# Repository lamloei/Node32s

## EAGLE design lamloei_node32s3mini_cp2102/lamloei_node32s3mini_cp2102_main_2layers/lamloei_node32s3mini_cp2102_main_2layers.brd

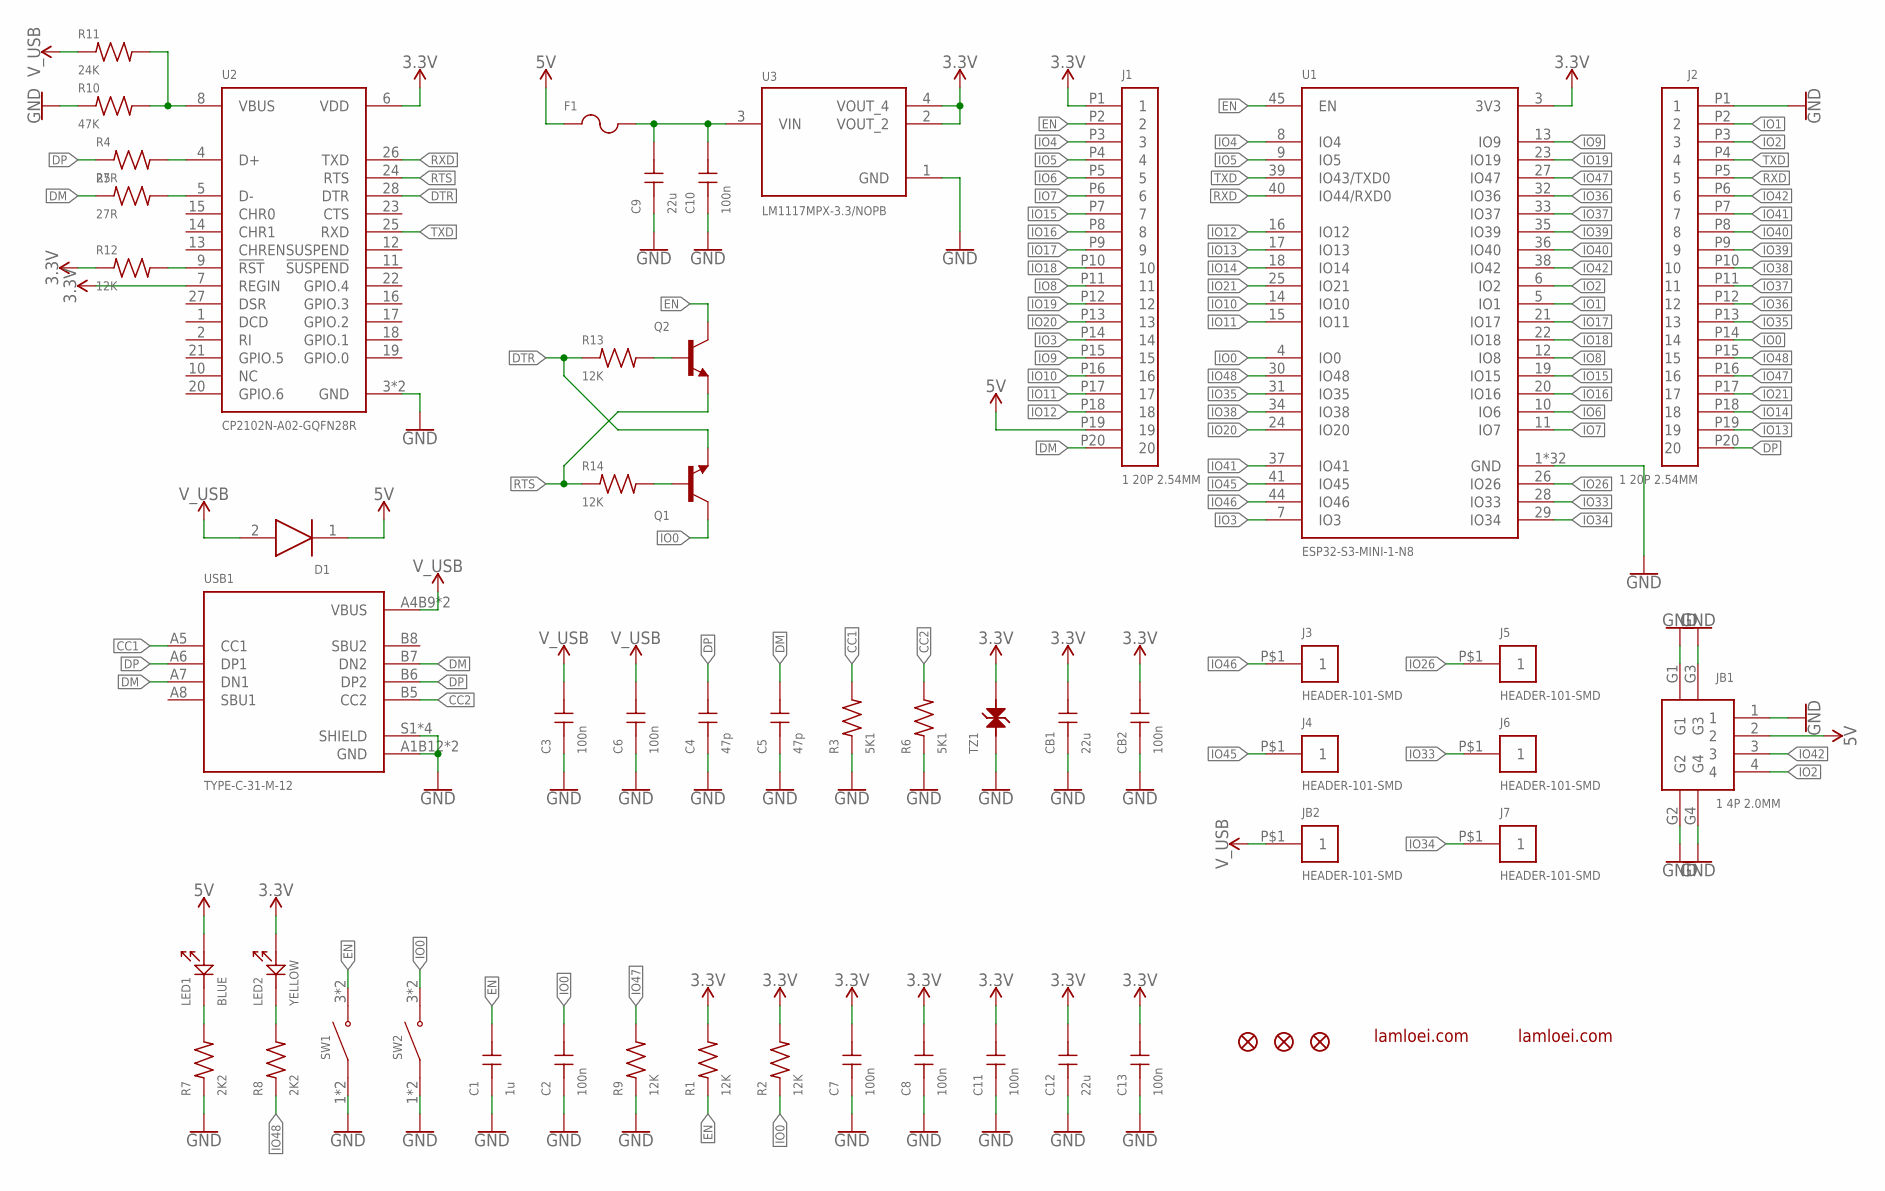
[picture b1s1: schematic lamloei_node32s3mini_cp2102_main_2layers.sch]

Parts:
C1: 1u; GRM155R70J105KA12D
C2, C3, C6, C7, C8, C10, C11, C13: 100n; GCM155R71H104KE02D
C4, C5: 47p; GCM1555C1H470JA16D
C9, C12: 22u; GCM21BR71H105KA03L
CB1: 22u; GCM21BR71H105KA03L
CB2: 100n; GCM155R71H104KE02D
D1: PMEG4050EP,115
F1: MF-NSMF050-2
J1, J2: 1 20P 2.54MM; HEADER-120
J3, J4, J5, J6, J7: HEADER-101-SMD
JB1: 1 4P 2.0MM; A2012WR-S-4P
JB2: HEADER-101-SMD
LED1: BLUE; 19-217BHC-ZL1M2RY3T
LED2: YELLOW; 19-213/Y2C-CQ2R2L/3T(CY)
Q1, Q2: BC847B,215
R1, R2, R9, R12, R13, R14: 12K; R0402
R3, R6: 5K1; R0402
R4, R5: 27R; R0402
R7, R8: 2K2; R0402
R10: 47K; R0402
R11: 24K; R0402
SW1, SW2: K2-1808SN-A4SW-01
TZ1: LXES15AAA1-153
U1: ESP32-S3-MINI-1-N8
U2: CP2102N-A02-GQFN28R
U3: LM1117MPX-3.3/NOPB
USB1: TYPE-C-31-M-12
ZFD1, ZFD2, ZFD3: FIDUCIAL1X2; FIDUCIAL-1X2
ZL1, ZL2: LAMLEOI_LOGO_3

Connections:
3.3V: C7.2, C8.2, C11.2, C12.2, C13.2, CB1.2, CB2.2, J1.P1 (1), LED2.2, R1.2, R2.2, R12.1, TZ1.2, U1.3 (3V3), U2.6 (VDD), U2.7 (REGIN), U3.2 (VOUT_2), U3.4 (VOUT_4)
5V: D1.1 (K), F1.1, J1.P19 (19), JB1.2, LED1.2
CC1: R3.2, USB1.A5 (CC1)
CC2: R6.2, USB1.B5 (CC2)
DM: C5.2, J1.P20 (20), R5.1, USB1.A7 (DN1), USB1.B7 (DN2)
DP: C4.2, J2.P20 (20), R4.1, USB1.A6 (DP1), USB1.B6 (DP2)
DTR: Q1.E, R13.1, U2.28 (DTR)
EN: C1.2, J1.P2 (2), Q2.C, R1.1, SW1.3 (NO), SW1.4 (NO), U1.45 (EN)
GND: C1.1, C2.1, C3.1, C4.1, C5.1, C6.1, C7.1, C8.1, C9.1, C10.1, C11.1, C12.1, C13.1, CB1.1, CB2.1, J2.P1 (1), JB1.1, JB1.G1, JB1.G2, JB1.G3, JB1.G4, R3.1, R6.1, R7.1, R9.1, R10.1, SW1.1 (COM), SW1.2 (COM), SW2.1 (COM), SW2.2 (COM), TZ1.1, U1.1 (GND), U1.2 (GND), U1.42 (GND), U1.43 (GND), U1.46 (GND), U1.47 (GND), U1.48 (GND), U1.49 (GND), U1.50 (GND), U1.51 (GND), U1.52 (GND), U1.53 (GND), U1.54 (GND), U1.55 (GND), U1.56 (GND), U1.57 (GND), U1.58 (GND), U1.59 (GND), U1.60 (GND), U1.61 (GND), U1.61_1 (GND), U1.61_2 (GND), U1.61_3 (GND), U1.61_4 (GND), U1.61_5 (GND), U1.61_6 (GND), U1.61_7 (GND), U1.61_8 (GND), U1.62 (GND), U1.63 (GND), U1.64 (GND), U1.65 (GND), U2.3 (GND), U2.29 (GND), U3.1 (GND), USB1.A1B12 (GND), USB1.B1A12 (GND), USB1.S1 (SHIELD), USB1.S2 (SHIELD), USB1.S3 (SHIELD), USB1.S4 (SHIELD)
GPIO.5: U2.21 (GPIO.5)
IO0: C2.2, J2.P14 (14), Q1.C, R2.1, SW2.3 (NO), SW2.4 (NO), U1.4 (IO0)
IO1: J2.P2 (2), U1.5 (IO1)
IO2: J2.P3 (3), JB1.4, U1.6 (IO2)
IO3: J1.P14 (14), U1.7 (IO3)
IO4: J1.P3 (3), U1.8 (IO4)
IO5: J1.P4 (4), U1.9 (IO5)
IO6: J1.P5 (5), U1.10 (IO6)
IO7: J1.P6 (6), U1.11 (IO7)
IO8: J1.P11 (11), U1.12 (IO8)
IO9: J1.P15 (15), U1.13 (IO9)
IO10: J1.P16 (16), U1.14 (IO10)
IO11: J1.P17 (17), U1.15 (IO11)
IO12: J1.P18 (18), U1.16 (IO12)
IO13: J2.P19 (19), U1.17 (IO13)
IO14: J2.P18 (18), U1.18 (IO14)
IO15: J1.P7 (7), U1.19 (IO15)
IO16: J1.P8 (8), U1.20 (IO16)
IO17: J1.P9 (9), U1.21 (IO17)
IO18: J1.P10 (10), U1.22 (IO18)
IO19: J1.P12 (12), U1.23 (IO19)
IO20: J1.P13 (13), U1.24 (IO20)
IO21: J2.P17 (17), U1.25 (IO21)
IO26: J5.P$1, U1.26 (IO26)
IO33: J6.P$1, U1.28 (IO33)
IO34: J7.P$1, U1.29 (IO34)
IO35: J2.P13 (13), U1.31 (IO35)
IO36: J2.P12 (12), U1.32 (IO36)
IO37: J2.P11 (11), U1.33 (IO37)
IO38: J2.P10 (10), U1.34 (IO38)
IO39: J2.P9 (9), U1.35 (IO39)
IO40: J2.P8 (8), U1.36 (IO40)
IO41: J2.P7 (7), U1.37 (IO41)
IO42: J2.P6 (6), JB1.3, U1.38 (IO42)
IO45: J4.P$1, U1.41 (IO45)
IO46: J3.P$1, U1.44 (IO46)
IO47: J2.P16 (16), R9.2, U1.27 (IO47)
IO48: J2.P15 (15), R8.1, U1.30 (IO48)
unnamed: R5.2, U2.5 (D-)
unnamed: R4.2, U2.4 (D+)
unnamed: C9.2, C10.2, F1.2, U3.3 (VIN)
unnamed: LED1.1, R7.2
unnamed: LED2.1, R8.2
unnamed: Q2.B, R13.2
unnamed: Q1.B, R14.2
unnamed: R12.2, U2.9 (!RST)
unnamed: R10.2, R11.2, U2.8 (VBUS)
RTS: Q2.E, R14.1, U2.24 (RTS)
RXD: J2.P5 (5), U1.40 (IO44/RXD0), U2.26 (TXD)
TXD: J2.P4 (4), U1.39 (IO43/TXD0), U2.25 (RXD)
V_USB: C3.2, C6.2, D1.2 (A), JB2.P$1, R11.1, USB1.A4B9 (VBUS), USB1.B4A9 (VBUS)

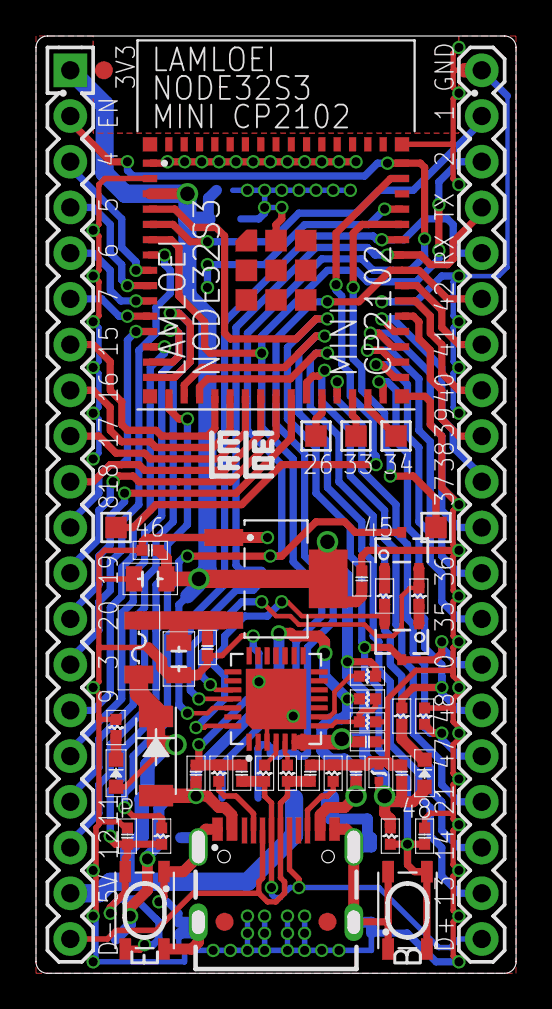
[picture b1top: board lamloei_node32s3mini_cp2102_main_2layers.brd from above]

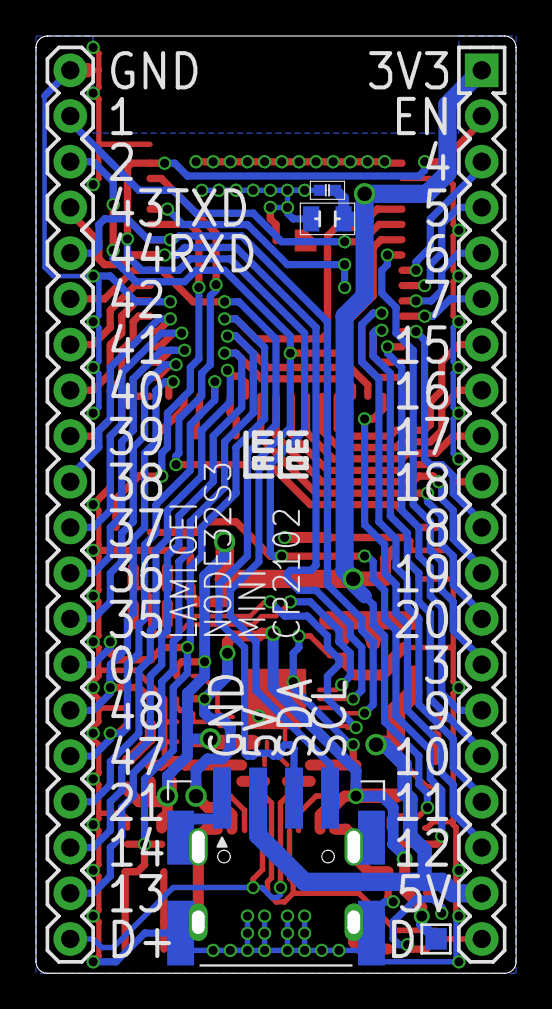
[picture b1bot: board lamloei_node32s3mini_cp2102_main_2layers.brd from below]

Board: 2 copper layers, 26.0 x 51.4 mm, 56 parts (5 on the bottom side), 59 nets.

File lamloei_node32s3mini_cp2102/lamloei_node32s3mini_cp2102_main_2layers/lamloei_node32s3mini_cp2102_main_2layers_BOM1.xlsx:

Comment | Designator | Footprint | LCSC Part #（optional）
Samsung - CL05A105KA5NQNC - 25V 1uF X5R ±10% | C1 | CAP_0402 | C52923
Samsung - CL05B104KO5NNNC - 16V 100nF X7R ±10% | C2, C3, C6, C7, C8, C10, C11, C13 | CAP_0402 | C1525
FH - 0402CG470J500NT - 50V 47pF C0G ±5% | C4, C5 | CAP_0402 | C1567
Samsung - CL21A106KAYNNNE - 25V 10UF X5R ±10% | C9 | CAP_0805 | C15850
Samsung - CL21A476MQYNNNE - 6.3V 47UF X5R ±20% | C12 | CAP_0805 | C16780
Extended - Nexperia - PMEG4020EP,115 - 40V 490mV@2A 2A (SBD) | D1 | SOD-128 | C456125
Extended - BOURNS - MF-NSMF050-2 - 13.2V 1A 1206 PTC | F1 | PTC_1206 | C75464
Everlight Elec - 19-217/BHC-ZL1M2RY/3T - Blue 465~475nm 0603 (LED) | LED1 | LED_0603 | C72041
Everlight Elec - 19-213/Y2C-CQ2R2L/3T(CY) - Yellow 585.5~591.5nm 0603 (LED) | LED2 | LED_0603 | C72038
CJ - S8050 J3Y - Transistors NPN 500mA 25V | Q1, Q2 | SOT-23-3 | C2146
UNI-ROYAL - 0402WGF1202TCE - 12kΩ ±1% 1/16W | R1, R2, R9, R12, R13, R14 | RES_0402 | C25752
UNI-ROYAL - 0402WGF5101TCE - 5.1kΩ ±1% 1/16W | R3, R6 | RES_0402 | C25905
UNI-ROYAL - 0402WGF220JTCE - 22Ω ±1% 1/16W | R4, R5 | RES_0402 | C25092
UNI-ROYAL - 0402WGF2201TCE - 2.2kΩ ±1% 1/16W | R7, R8 | RES_0402 | C25879
UNI-ROYAL - 0402WGF4702TCE - 47kΩ ±1% 1/16W | R10 | RES_0402 | C25792
UNI-ROYAL - 0402WGF2402TCE - 24kΩ ±1% 1/16W | R11 | RES_0402 | C25769
Extended - Korean Hroparts Elec - K2-1808UN-A4SW-04 - SPST 50mA @ 12VDC | SW1 | SMD-4_3.25x2.5x4.2P | C145878
Extended - Korean Hroparts Elec - K2-1808GN-A4SW-04 - SPST 50mA @ 12VDC | SW2 | SMD-4_3.25x2.5x4.2P | C283535
Extended - Murata - LXES15AAA1-153 - Diodes - ESD 0402 | TZ1 | TVS_0402 | C86141
Extended - Espressif - ESP32-S3-MINI-1U-N8 - Module WiFi Modules | U1 | QFN-73_EP_15.4x15.4x0.85P | C2980299
SILICON LABS - CP2102-GMR - Transceiver 1Mbps USB 1/1 | U2 | QFN-28_EP_5.0x5.0x0.5P | C6568
AMS - AMS1117-3.3 - 1A 1.3V@(800mA) Fixed 3.3V~3.3V Positive 1 (LDO) | U3 | SOT-223 | C6186
Extended - Korean Hroparts Elec - TYPE-C-31-M-12 - USB - Type C Female | USB1 | TYPE-C-31_L8.94_W7.3 | C165948

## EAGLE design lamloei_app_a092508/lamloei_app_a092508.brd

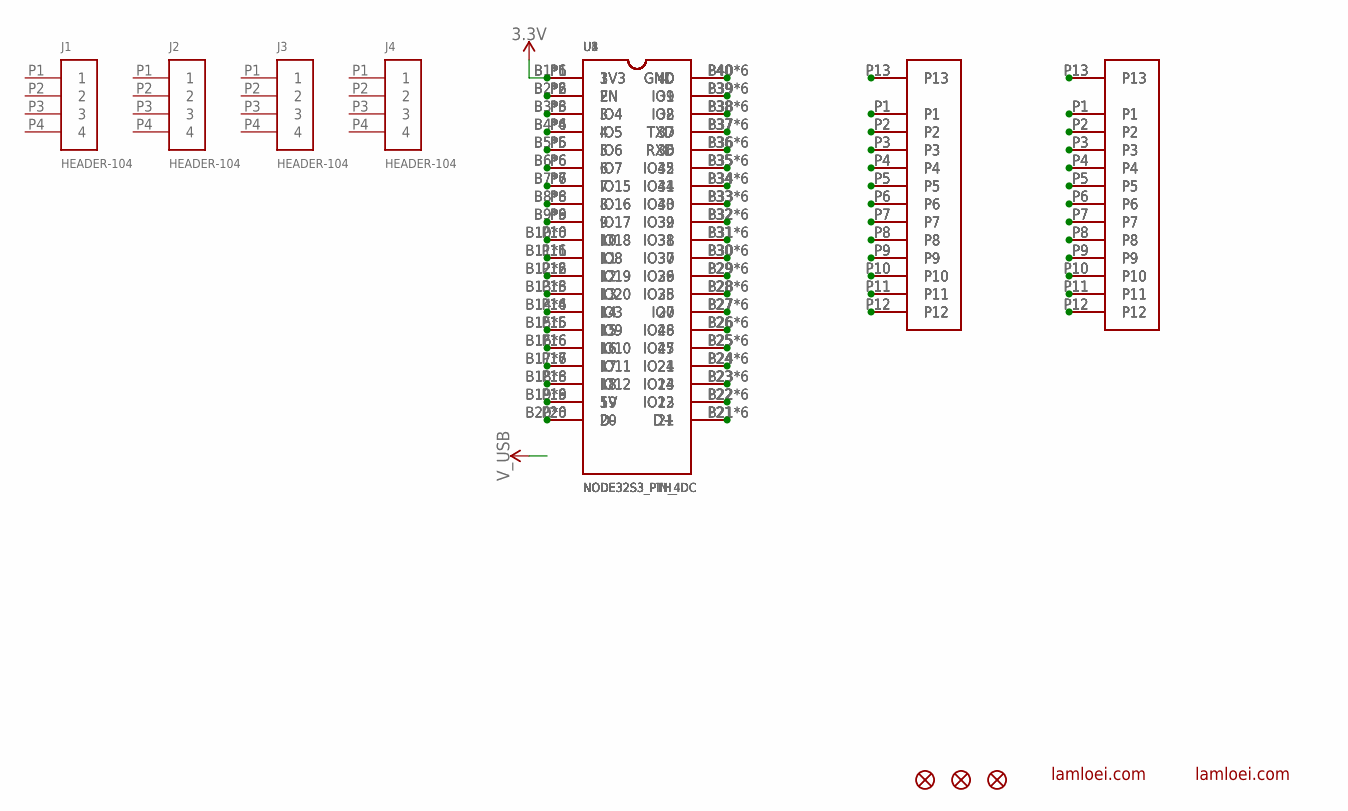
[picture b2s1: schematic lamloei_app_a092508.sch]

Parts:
J1, J2, J3, J4: HEADER-104
U1, U2: NODE32S3_PIN_4; NODE32S3_PTH_4
U3, U4, U5: NODE32S3_PTH_IDC
X1, X4: 5EHDRC-12P-508
X2, X5: 5EHDRC-12P-5.08MM
X3, X6: 5EHDRC-12P-2-508
ZFD1, ZFD2, ZFD3: FIDUCIAL1X2; FIDUCIAL-1X2
ZL1, ZL2: LAMLEOI_LOGO_3

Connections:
3.3V: U1.B1 (1), U1.N1 (1), U1.O1 (1), U1.P1 (1), U1.Q1 (1), U1.T1 (1), U2.B1 (1), U2.N1 (1), U2.O1 (1), U2.P1 (1), U2.Q1 (1), U2.T1 (1), U3.P1 (3V3), U4.P1 (3V3), U5.P1 (3V3)
unnamed: X1.P1, X2.P1, X3.P1
unnamed: U1.B2 (2), U1.N2 (2), U1.O2 (2), U1.P2 (2), U1.Q2 (2), U1.T2 (2), U2.B2 (2), U2.N2 (2), U2.O2 (2), U2.P2 (2), U2.Q2 (2), U2.T2 (2), U3.P2 (EN), U4.P2 (EN), U5.P2 (EN)
unnamed: U1.B3 (3), U1.N3 (3), U1.O3 (3), U1.P3 (3), U1.Q3 (3), U1.T3 (3), U2.B3 (3), U2.N3 (3), U2.O3 (3), U2.P3 (3), U2.Q3 (3), U2.T3 (3), U3.P3 (IO4), U4.P3 (IO4), U5.P3 (IO4)
unnamed: U1.B4 (4), U1.N4 (4), U1.O4 (4), U1.P4 (4), U1.Q4 (4), U1.T4 (4), U2.B4 (4), U2.N4 (4), U2.O4 (4), U2.P4 (4), U2.Q4 (4), U2.T4 (4), U3.P4 (IO5), U4.P4 (IO5), U5.P4 (IO5)
unnamed: U1.B5 (5), U1.N5 (5), U1.O5 (5), U1.P5 (5), U1.Q5 (5), U1.T5 (5), U2.B5 (5), U2.N5 (5), U2.O5 (5), U2.P5 (5), U2.Q5 (5), U2.T5 (5), U3.P5 (IO6), U4.P5 (IO6), U5.P5 (IO6)
unnamed: U1.B6 (6), U1.N6 (6), U1.O6 (6), U1.P6 (6), U1.Q6 (6), U1.T6 (6), U2.B6 (6), U2.N6 (6), U2.O6 (6), U2.P6 (6), U2.Q6 (6), U2.T6 (6), U3.P6 (IO7), U4.P6 (IO7), U5.P6 (IO7)
unnamed: U1.B7 (7), U1.N7 (7), U1.O7 (7), U1.P7 (7), U1.Q7 (7), U1.T7 (7), U2.B7 (7), U2.N7 (7), U2.O7 (7), U2.P7 (7), U2.Q7 (7), U2.T7 (7), U3.P7 (IO15), U4.P7 (IO15), U5.P7 (IO15)
unnamed: U1.B8 (8), U1.N8 (8), U1.O8 (8), U1.P8 (8), U1.Q8 (8), U1.T8 (8), U2.B8 (8), U2.N8 (8), U2.O8 (8), U2.P8 (8), U2.Q8 (8), U2.T8 (8), U3.P8 (IO16), U4.P8 (IO16), U5.P8 (IO16)
unnamed: U1.B9 (9), U1.N9 (9), U1.O9 (9), U1.P9 (9), U1.Q9 (9), U1.T9 (9), U2.B9 (9), U2.N9 (9), U2.O9 (9), U2.P9 (9), U2.Q9 (9), U2.T9 (9), U3.P9 (IO17), U4.P9 (IO17), U5.P9 (IO17)
unnamed: U1.B10 (10), U1.N10 (10), U1.O10 (10), U1.P10 (10), U1.Q10 (10), U1.T10 (10), U2.B10 (10), U2.N10 (10), U2.O10 (10), U2.P10 (10), U2.Q10 (10), U2.T10 (10), U3.P10 (IO18), U4.P10 (IO18), U5.P10 (IO18)
unnamed: U1.B11 (11), U1.N11 (11), U1.O11 (11), U1.P11 (11), U1.Q11 (11), U1.T11 (11), U2.B11 (11), U2.N11 (11), U2.O11 (11), U2.P11 (11), U2.Q11 (11), U2.T11 (11), U3.P11 (IO8), U4.P11 (IO8), U5.P11 (IO8)
unnamed: U1.B12 (12), U1.N12 (12), U1.O12 (12), U1.P12 (12), U1.Q12 (12), U1.T12 (12), U2.B12 (12), U2.N12 (12), U2.O12 (12), U2.P12 (12), U2.Q12 (12), U2.T12 (12), U3.P12 (IO19), U4.P12 (IO19), U5.P12 (IO19)
unnamed: U1.B13 (13), U1.N13 (13), U1.O13 (13), U1.P13 (13), U1.Q13 (13), U1.T13 (13), U2.B13 (13), U2.N13 (13), U2.O13 (13), U2.P13 (13), U2.Q13 (13), U2.T13 (13), U3.P13 (IO20), U4.P13 (IO20), U5.P13 (IO20)
unnamed: U1.B14 (14), U1.N14 (14), U1.O14 (14), U1.P14 (14), U1.Q14 (14), U1.T14 (14), U2.B14 (14), U2.N14 (14), U2.O14 (14), U2.P14 (14), U2.Q14 (14), U2.T14 (14), U3.P14 (IO3), U4.P14 (IO3), U5.P14 (IO3)
unnamed: U1.B15 (15), U1.N15 (15), U1.O15 (15), U1.P15 (15), U1.Q15 (15), U1.T15 (15), U2.B15 (15), U2.N15 (15), U2.O15 (15), U2.P15 (15), U2.Q15 (15), U2.T15 (15), U3.P15 (IO9), U4.P15 (IO9), U5.P15 (IO9)
unnamed: U1.B17 (17), U1.N17 (17), U1.O17 (17), U1.P17 (17), U1.Q17 (17), U1.T17 (17), U2.B17 (17), U2.N17 (17), U2.O17 (17), U2.P17 (17), U2.Q17 (17), U2.T17 (17), U3.P17 (IO11), U4.P17 (IO11), U5.P17 (IO11)
unnamed: U1.B16 (16), U1.N16 (16), U1.O16 (16), U1.P16 (16), U1.Q16 (16), U1.T16 (16), U2.B16 (16), U2.N16 (16), U2.O16 (16), U2.P16 (16), U2.Q16 (16), U2.T16 (16), U3.P16 (IO10), U4.P16 (IO10), U5.P16 (IO10)
unnamed: U1.B18 (18), U1.N18 (18), U1.O18 (18), U1.P18 (18), U1.Q18 (18), U1.T18 (18), U2.B18 (18), U2.N18 (18), U2.O18 (18), U2.P18 (18), U2.Q18 (18), U2.T18 (18), U3.P18 (IO12), U4.P18 (IO12), U5.P18 (IO12)
unnamed: U1.B19 (19), U1.N19 (19), U1.O19 (19), U1.P19 (19), U1.Q19 (19), U1.T19 (19), U2.B19 (19), U2.N19 (19), U2.O19 (19), U2.P19 (19), U2.Q19 (19), U2.T19 (19), U3.P19 (5V), U4.P19 (5V), U5.P19 (5V)
unnamed: U1.B20 (20), U1.N20 (20), U1.O20 (20), U1.P20 (20), U1.Q20 (20), U1.T20 (20), U2.B20 (20), U2.N20 (20), U2.O20 (20), U2.P20 (20), U2.Q20 (20), U2.T20 (20), U3.P20 (D-), U4.P20 (D-), U5.P20 (D-)
unnamed: U1.B21 (21), U1.N21 (21), U1.O21 (21), U1.P21 (21), U1.Q21 (21), U1.T21 (21), U2.B21 (21), U2.N21 (21), U2.O21 (21), U2.P21 (21), U2.Q21 (21), U2.T21 (21), U3.P21 (D+), U4.P21 (D+), U5.P21 (D+)
unnamed: U1.B22 (22), U1.N22 (22), U1.O22 (22), U1.P22 (22), U1.Q22 (22), U1.T22 (22), U2.B22 (22), U2.N22 (22), U2.O22 (22), U2.P22 (22), U2.Q22 (22), U2.T22 (22), U3.P22 (IO13), U4.P22 (IO13), U5.P22 (IO13)
unnamed: U1.B23 (23), U1.N23 (23), U1.O23 (23), U1.P23 (23), U1.Q23 (23), U1.T23 (23), U2.B23 (23), U2.N23 (23), U2.O23 (23), U2.P23 (23), U2.Q23 (23), U2.T23 (23), U3.P23 (IO14), U4.P23 (IO14), U5.P23 (IO14)
unnamed: U1.B24 (24), U1.N24 (24), U1.O24 (24), U1.P24 (24), U1.Q24 (24), U1.T24 (24), U2.B24 (24), U2.N24 (24), U2.O24 (24), U2.P24 (24), U2.Q24 (24), U2.T24 (24), U3.P24 (IO21), U4.P24 (IO21), U5.P24 (IO21)
unnamed: U1.B25 (25), U1.N25 (25), U1.O25 (25), U1.P25 (25), U1.Q25 (25), U1.T25 (25), U2.B25 (25), U2.N25 (25), U2.O25 (25), U2.P25 (25), U2.Q25 (25), U2.T25 (25), U3.P25 (IO47), U4.P25 (IO47), U5.P25 (IO47)
unnamed: U1.B26 (26), U1.N26 (26), U1.O26 (26), U1.P26 (26), U1.Q26 (26), U1.T26 (26), U2.B26 (26), U2.N26 (26), U2.O26 (26), U2.P26 (26), U2.Q26 (26), U2.T26 (26), U3.P26 (IO48), U4.P26 (IO48), U5.P26 (IO48)
unnamed: U1.B27 (27), U1.N27 (27), U1.O27 (27), U1.P27 (27), U1.Q27 (27), U1.T27 (27), U2.B27 (27), U2.N27 (27), U2.O27 (27), U2.P27 (27), U2.Q27 (27), U2.T27 (27), U3.P27 (IO0), U4.P27 (IO0), U5.P27 (IO0)
unnamed: U1.B28 (28), U1.N28 (28), U1.O28 (28), U1.P28 (28), U1.Q28 (28), U1.T28 (28), U2.B28 (28), U2.N28 (28), U2.O28 (28), U2.P28 (28), U2.Q28 (28), U2.T28 (28), U3.P28 (IO35), U4.P28 (IO35), U5.P28 (IO35)
unnamed: U1.B29 (29), U1.N29 (29), U1.O29 (29), U1.P29 (29), U1.Q29 (29), U1.T29 (29), U2.B29 (29), U2.N29 (29), U2.O29 (29), U2.P29 (29), U2.Q29 (29), U2.T29 (29), U3.P29 (IO36), U4.P29 (IO36), U5.P29 (IO36)
unnamed: U1.B30 (30), U1.N30 (30), U1.O30 (30), U1.P30 (30), U1.Q30 (30), U1.T30 (30), U2.B30 (30), U2.N30 (30), U2.O30 (30), U2.P30 (30), U2.Q30 (30), U2.T30 (30), U3.P30 (IO37), U4.P30 (IO37), U5.P30 (IO37)
unnamed: U1.B31 (31), U1.N31 (31), U1.O31 (31), U1.P31 (31), U1.Q31 (31), U1.T31 (31), U2.B31 (31), U2.N31 (31), U2.O31 (31), U2.P31 (31), U2.Q31 (31), U2.T31 (31), U3.P31 (IO38), U4.P31 (IO38), U5.P31 (IO38)
unnamed: U1.B32 (32), U1.N32 (32), U1.O32 (32), U1.P32 (32), U1.Q32 (32), U1.T32 (32), U2.B32 (32), U2.N32 (32), U2.O32 (32), U2.P32 (32), U2.Q32 (32), U2.T32 (32), U3.P32 (IO39), U4.P32 (IO39), U5.P32 (IO39)
unnamed: U1.B33 (33), U1.N33 (33), U1.O33 (33), U1.P33 (33), U1.Q33 (33), U1.T33 (33), U2.B33 (33), U2.N33 (33), U2.O33 (33), U2.P33 (33), U2.Q33 (33), U2.T33 (33), U3.P33 (IO40), U4.P33 (IO40), U5.P33 (IO40)
unnamed: U1.B34 (34), U1.N34 (34), U1.O34 (34), U1.P34 (34), U1.Q34 (34), U1.T34 (34), U2.B34 (34), U2.N34 (34), U2.O34 (34), U2.P34 (34), U2.Q34 (34), U2.T34 (34), U3.P34 (IO41), U4.P34 (IO41), U5.P34 (IO41)
unnamed: U1.B35 (35), U1.N35 (35), U1.O35 (35), U1.P35 (35), U1.Q35 (35), U1.T35 (35), U2.B35 (35), U2.N35 (35), U2.O35 (35), U2.P35 (35), U2.Q35 (35), U2.T35 (35), U3.P35 (IO42), U4.P35 (IO42), U5.P35 (IO42)
unnamed: U1.B36 (36), U1.N36 (36), U1.O36 (36), U1.P36 (36), U1.Q36 (36), U1.T36 (36), U2.B36 (36), U2.N36 (36), U2.O36 (36), U2.P36 (36), U2.Q36 (36), U2.T36 (36), U3.P36 (RXD), U4.P36 (RXD), U5.P36 (RXD)
unnamed: U1.B37 (37), U1.N37 (37), U1.O37 (37), U1.P37 (37), U1.Q37 (37), U1.T37 (37), U2.B37 (37), U2.N37 (37), U2.O37 (37), U2.P37 (37), U2.Q37 (37), U2.T37 (37), U3.P37 (TXD), U4.P37 (TXD), U5.P37 (TXD)
unnamed: U1.B38 (38), U1.N38 (38), U1.O38 (38), U1.P38 (38), U1.Q38 (38), U1.T38 (38), U2.B38 (38), U2.N38 (38), U2.O38 (38), U2.P38 (38), U2.Q38 (38), U2.T38 (38), U3.P38 (IO2), U4.P38 (IO2), U5.P38 (IO2)
unnamed: U1.B39 (39), U1.N39 (39), U1.O39 (39), U1.P39 (39), U1.Q39 (39), U1.T39 (39), U2.B39 (39), U2.N39 (39), U2.O39 (39), U2.P39 (39), U2.Q39 (39), U2.T39 (39), U3.P39 (IO1), U4.P39 (IO1), U5.P39 (IO1)
unnamed: U1.B40 (40), U1.N40 (40), U1.O40 (40), U1.P40 (40), U1.Q40 (40), U1.T40 (40), U2.B40 (40), U2.N40 (40), U2.O40 (40), U2.P40 (40), U2.Q40 (40), U2.T40 (40), U3.P40 (GND), U4.P40 (GND), U5.P40 (GND)
unnamed: X1.P2, X2.P2, X3.P2
unnamed: X1.P3, X2.P3, X3.P3
unnamed: X1.P4, X2.P4, X3.P4
unnamed: X1.P5, X2.P5, X3.P5
unnamed: X1.P6, X2.P6, X3.P6
unnamed: X1.P7, X2.P7, X3.P7
unnamed: X1.P8, X2.P8, X3.P8
unnamed: X1.P9, X2.P9, X3.P9
unnamed: X1.P10, X2.P10, X3.P10
unnamed: X1.P11, X2.P11, X3.P11
unnamed: X1.P12, X2.P12, X3.P12
unnamed: X1.P13, X2.P13, X3.P13
unnamed: X4.P1, X5.P1, X6.P1
unnamed: X4.P2, X5.P2, X6.P2
unnamed: X4.P3, X5.P3, X6.P3
unnamed: X4.P4, X5.P4, X6.P4
unnamed: X4.P5, X5.P5, X6.P5
unnamed: X4.P6, X5.P6, X6.P6
unnamed: X4.P7, X5.P7, X6.P7
unnamed: X4.P8, X5.P8, X6.P8
unnamed: X4.P9, X5.P9, X6.P9
unnamed: X4.P10, X5.P10, X6.P10
unnamed: X4.P11, X5.P11, X6.P11
unnamed: X4.P12, X5.P12, X6.P12
unnamed: X4.P13, X5.P13, X6.P13

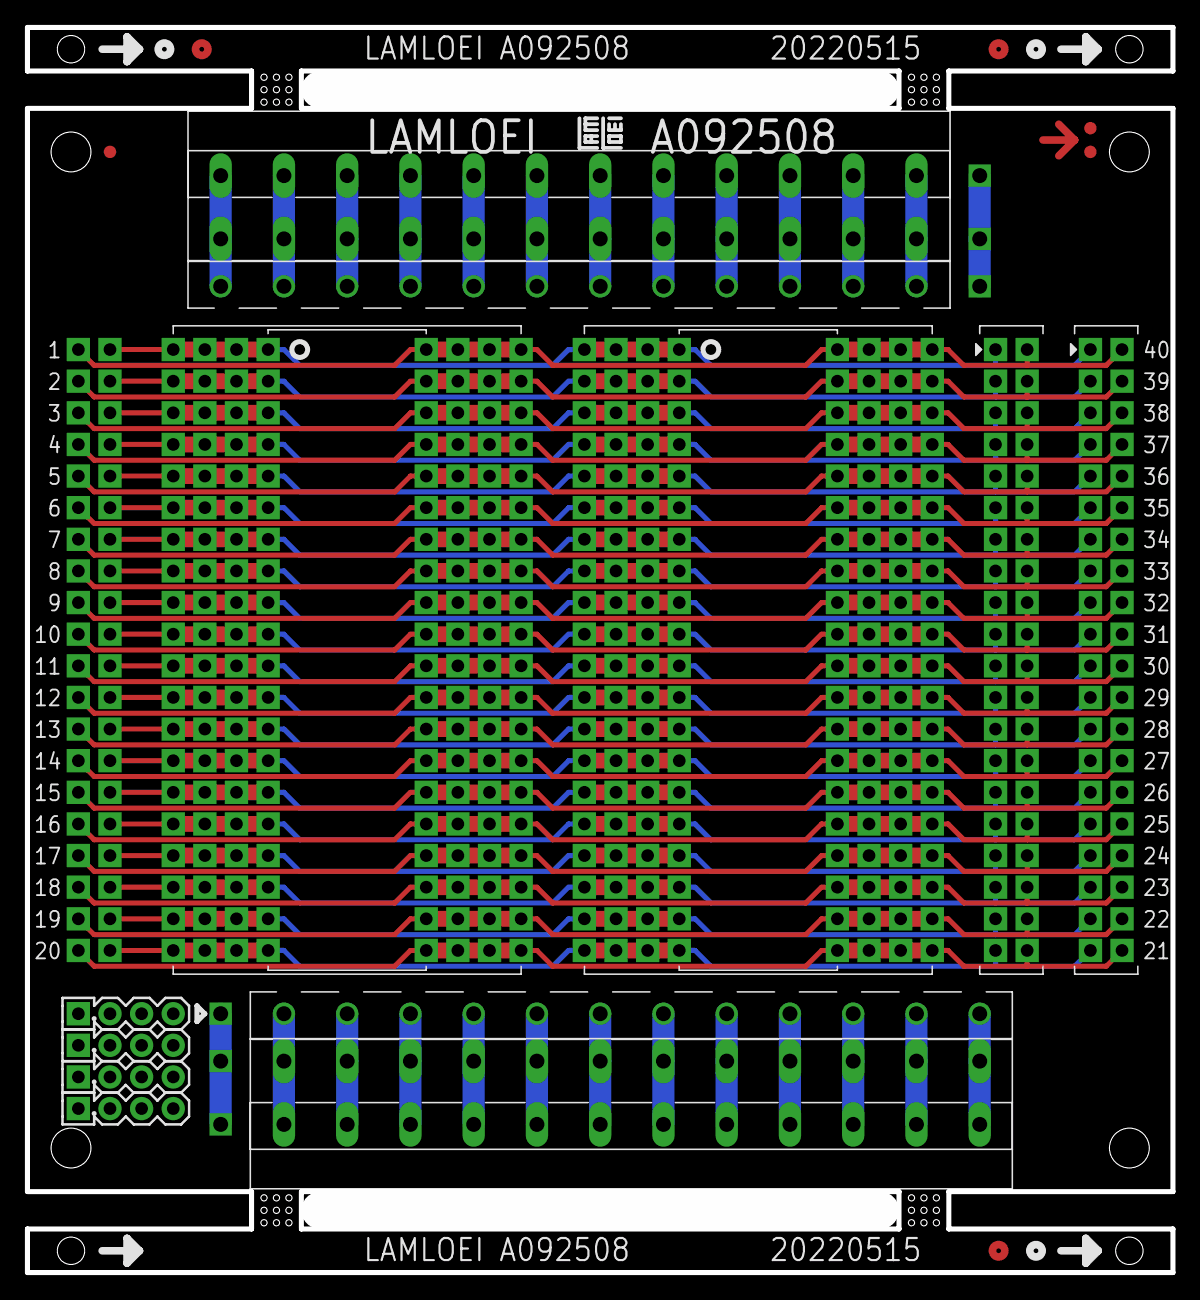
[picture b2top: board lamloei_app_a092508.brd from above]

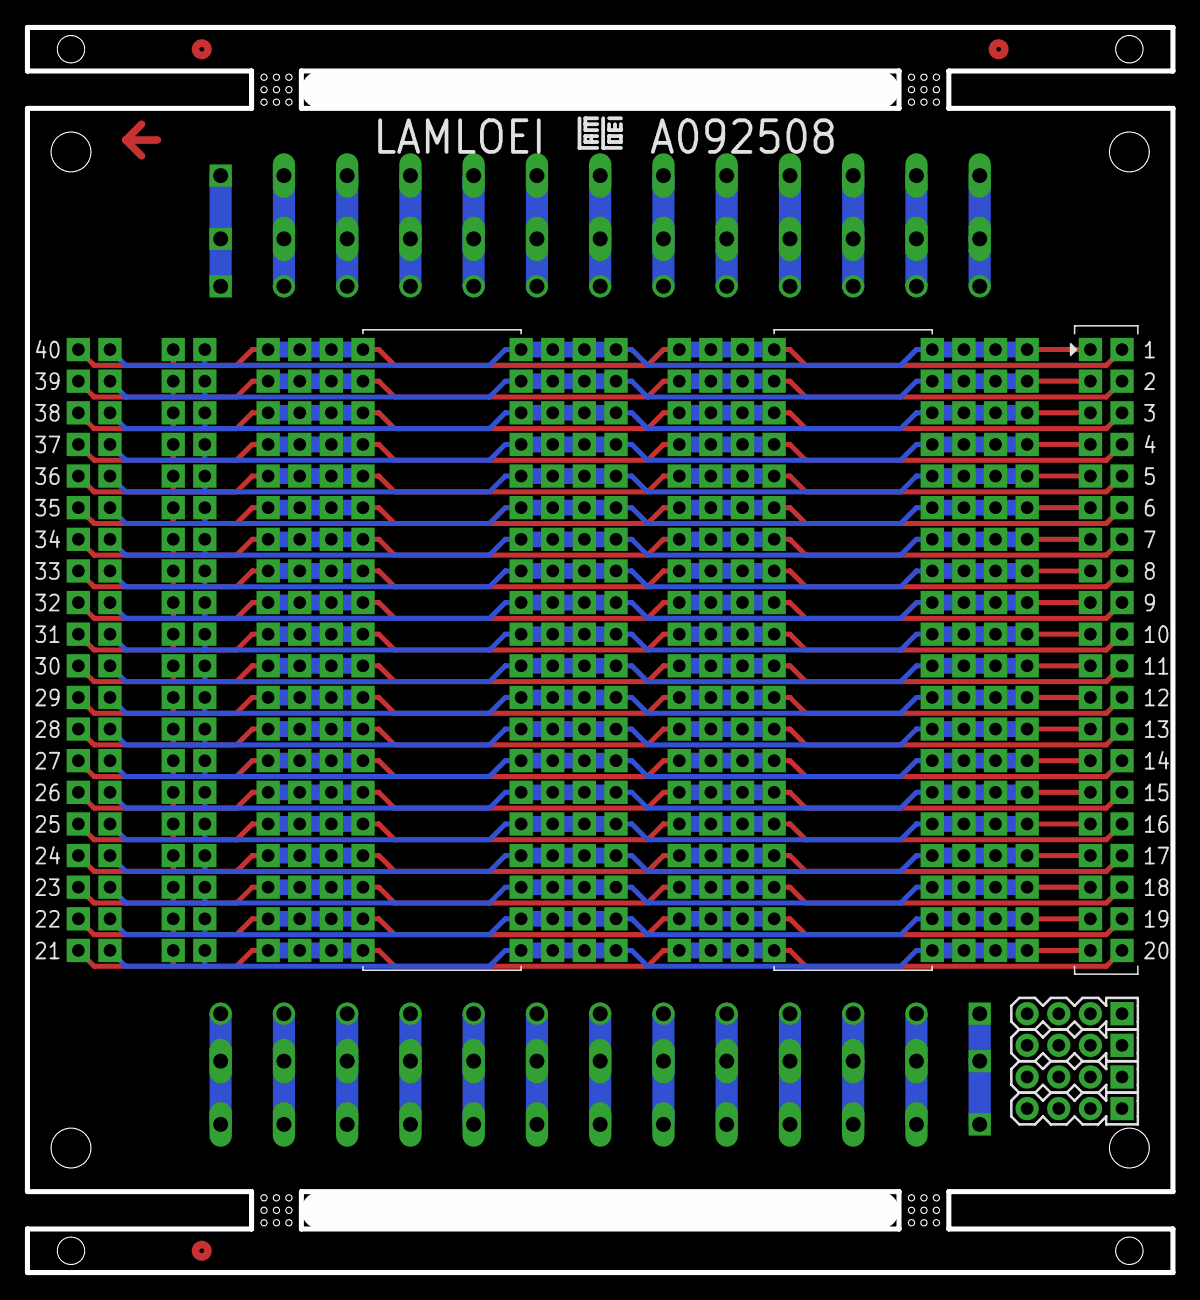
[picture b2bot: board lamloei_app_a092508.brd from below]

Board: 2 copper layers, 89.4 x 97.4 mm, 20 parts (2 on the bottom side), 66 nets.

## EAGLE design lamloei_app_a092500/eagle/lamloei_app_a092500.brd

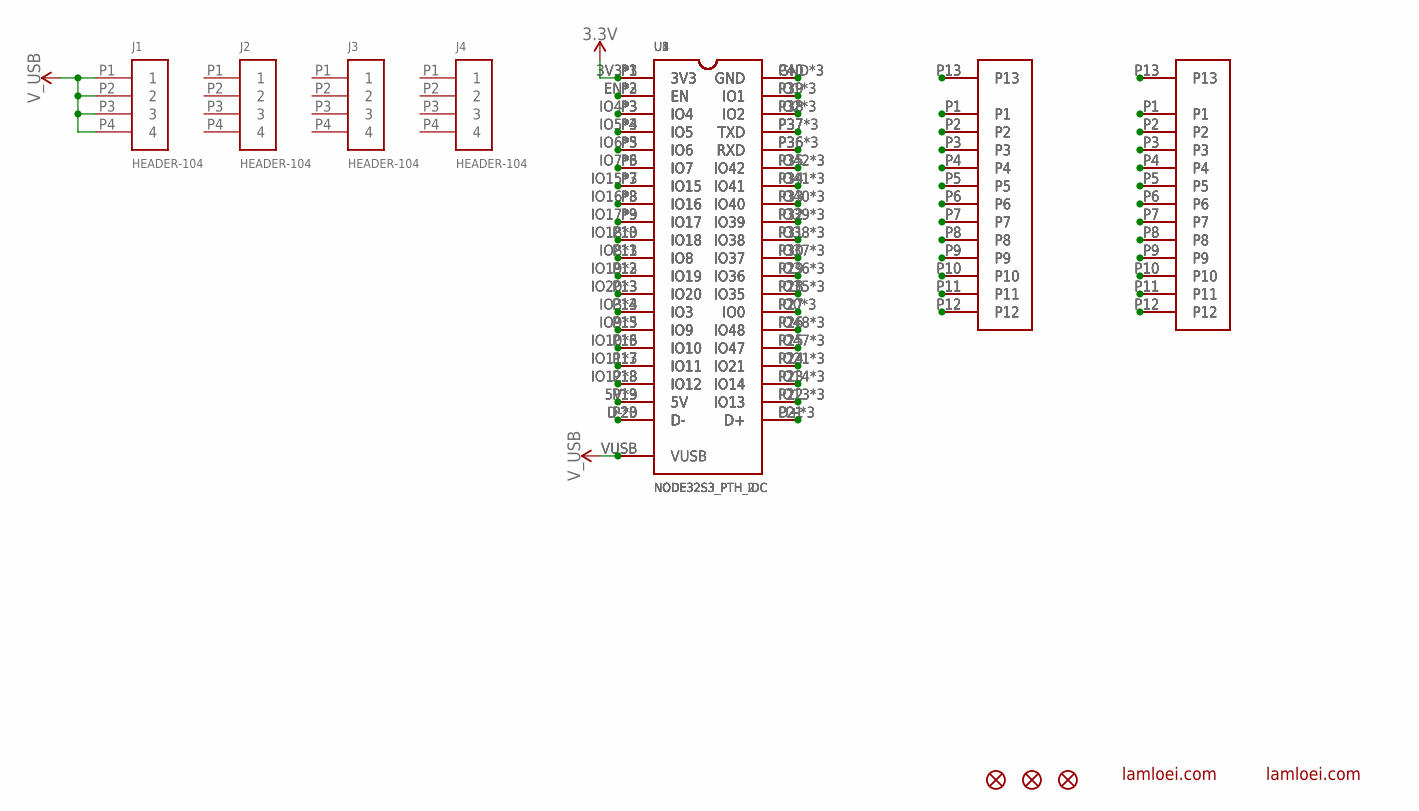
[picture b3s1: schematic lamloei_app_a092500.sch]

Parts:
J1, J2, J3, J4: HEADER-104
U1, U2: NODE32S3_PTH_2
U3, U4, U5: NODE32S3_PTH_IDC
X1, X4: 5EHDRC-12P
X2, X5: 5EHDRC-12P-5.08MM
X3, X6: 5EHDRC-12P-2
ZFD1, ZFD2, ZFD3: FIDUCIAL1X2; FIDUCIAL-1X2
ZL1, ZL2: LAMLEOI_LOGO_3

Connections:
3.3V: U1.3V3, U1.P1 (3V3), U1.Q1 (3V3), U2.3V3, U2.P1 (3V3), U2.Q1 (3V3), U3.P1 (3V3), U4.P1 (3V3), U5.P1 (3V3)
unnamed: U1.EN, U1.P2 (EN), U1.Q2 (EN), U2.EN, U2.P2 (EN), U2.Q2 (EN), U3.P2 (EN), U4.P2 (EN), U5.P2 (EN)
unnamed: U1.IO4, U1.P3 (IO4), U1.Q3 (IO4), U2.IO4, U2.P3 (IO4), U2.Q3 (IO4), U3.P3 (IO4), U4.P3 (IO4), U5.P3 (IO4)
unnamed: U1.IO5, U1.P4 (IO5), U1.Q4 (IO5), U2.IO5, U2.P4 (IO5), U2.Q4 (IO5), U3.P4 (IO5), U4.P4 (IO5), U5.P4 (IO5)
unnamed: U1.IO6, U1.P5 (IO6), U1.Q5 (IO6), U2.IO6, U2.P5 (IO6), U2.Q5 (IO6), U3.P5 (IO6), U4.P5 (IO6), U5.P5 (IO6)
unnamed: U1.IO7, U1.P6 (IO7), U1.Q6 (IO7), U2.IO7, U2.P6 (IO7), U2.Q6 (IO7), U3.P6 (IO7), U4.P6 (IO7), U5.P6 (IO7)
unnamed: U1.IO15, U1.P7 (IO15), U1.Q7 (IO15), U2.IO15, U2.P7 (IO15), U2.Q7 (IO15), U3.P7 (IO15), U4.P7 (IO15), U5.P7 (IO15)
unnamed: U1.IO16, U1.P8 (IO16), U1.Q8 (IO16), U2.IO16, U2.P8 (IO16), U2.Q8 (IO16), U3.P8 (IO16), U4.P8 (IO16), U5.P8 (IO16)
unnamed: U1.IO17, U1.P9 (IO17), U1.Q9 (IO17), U2.IO17, U2.P9 (IO17), U2.Q9 (IO17), U3.P9 (IO17), U4.P9 (IO17), U5.P9 (IO17)
unnamed: U1.IO18, U1.P10 (IO18), U1.Q10 (IO18), U2.IO18, U2.P10 (IO18), U2.Q10 (IO18), U3.P10 (IO18), U4.P10 (IO18), U5.P10 (IO18)
unnamed: U1.IO8, U1.P11 (IO8), U1.Q11 (IO8), U2.IO8, U2.P11 (IO8), U2.Q11 (IO8), U3.P11 (IO8), U4.P11 (IO8), U5.P11 (IO8)
unnamed: U1.IO19, U1.P12 (IO19), U1.Q12 (IO19), U2.IO19, U2.P12 (IO19), U2.Q12 (IO19), U3.P12 (IO19), U4.P12 (IO19), U5.P12 (IO19)
unnamed: U1.IO20, U1.P13 (IO20), U1.Q13 (IO20), U2.IO20, U2.P13 (IO20), U2.Q13 (IO20), U3.P13 (IO20), U4.P13 (IO20), U5.P13 (IO20)
unnamed: U1.IO3, U1.P14 (IO3), U1.Q14 (IO3), U2.IO3, U2.P14 (IO3), U2.Q14 (IO3), U3.P14 (IO3), U4.P14 (IO3), U5.P14 (IO3)
unnamed: U1.IO9, U1.P15 (IO9), U1.Q15 (IO9), U2.IO9, U2.P15 (IO9), U2.Q15 (IO9), U3.P15 (IO9), U4.P15 (IO9), U5.P15 (IO9)
unnamed: U1.IO11, U1.P17 (IO11), U1.Q17 (IO11), U2.IO11, U2.P17 (IO11), U2.Q17 (IO11), U3.P17 (IO11), U4.P17 (IO11), U5.P17 (IO11)
unnamed: U1.IO10, U1.P16 (IO10), U1.Q16 (IO10), U2.IO10, U2.P16 (IO10), U2.Q16 (IO10), U3.P16 (IO10), U4.P16 (IO10), U5.P16 (IO10)
unnamed: U1.IO12, U1.P18 (IO12), U1.Q18 (IO12), U2.IO12, U2.P18 (IO12), U2.Q18 (IO12), U3.P18 (IO12), U4.P18 (IO12), U5.P18 (IO12)
unnamed: U1.5V, U1.P19 (5V), U1.Q19 (5V), U2.5V, U2.P19 (5V), U2.Q19 (5V), U3.P19 (5V), U4.P19 (5V), U5.P19 (5V)
unnamed: U1.D-, U1.P20 (D-), U1.Q20 (D-), U2.D-, U2.P20 (D-), U2.Q20 (D-), U3.P20 (D-), U4.P20 (D-), U5.P20 (D-)
unnamed: U1.D+, U1.P21 (D+), U1.Q21 (D+), U2.D+, U2.P21 (D+), U2.Q21 (D+), U3.P21 (D+), U4.P21 (D+), U5.P21 (D+)
unnamed: U1.IO13, U1.P22 (IO13), U1.Q22 (IO13), U2.IO13, U2.P22 (IO13), U2.Q22 (IO13), U3.P22 (IO13), U4.P22 (IO13), U5.P22 (IO13)
unnamed: U1.IO14, U1.P23 (IO14), U1.Q23 (IO14), U2.IO14, U2.P23 (IO14), U2.Q23 (IO14), U3.P23 (IO14), U4.P23 (IO14), U5.P23 (IO14)
unnamed: U1.IO21, U1.P24 (IO21), U1.Q24 (IO21), U2.IO21, U2.P24 (IO21), U2.Q24 (IO21), U3.P24 (IO21), U4.P24 (IO21), U5.P24 (IO21)
unnamed: U1.IO47, U1.P25 (IO47), U1.Q25 (IO47), U2.IO47, U2.P25 (IO47), U2.Q25 (IO47), U3.P25 (IO47), U4.P25 (IO47), U5.P25 (IO47)
unnamed: U1.IO48, U1.P26 (IO48), U1.Q26 (IO48), U2.IO48, U2.P26 (IO48), U2.Q26 (IO48), U3.P26 (IO48), U4.P26 (IO48), U5.P26 (IO48)
unnamed: U1.IO0, U1.P27 (IO0), U1.Q27 (IO0), U2.IO0, U2.P27 (IO0), U2.Q27 (IO0), U3.P27 (IO0), U4.P27 (IO0), U5.P27 (IO0)
unnamed: U1.IO35, U1.P28 (IO35), U1.Q28 (IO35), U2.IO35, U2.P28 (IO35), U2.Q28 (IO35), U3.P28 (IO35), U4.P28 (IO35), U5.P28 (IO35)
unnamed: U1.IO36, U1.P29 (IO36), U1.Q29 (IO36), U2.IO36, U2.P29 (IO36), U2.Q29 (IO36), U3.P29 (IO36), U4.P29 (IO36), U5.P29 (IO36)
unnamed: U1.IO37, U1.P30 (IO37), U1.Q30 (IO37), U2.IO37, U2.P30 (IO37), U2.Q30 (IO37), U3.P30 (IO37), U4.P30 (IO37), U5.P30 (IO37)
unnamed: U1.IO38, U1.P31 (IO38), U1.Q31 (IO38), U2.IO38, U2.P31 (IO38), U2.Q31 (IO38), U3.P31 (IO38), U4.P31 (IO38), U5.P31 (IO38)
unnamed: U1.IO39, U1.P32 (IO39), U1.Q32 (IO39), U2.IO39, U2.P32 (IO39), U2.Q32 (IO39), U3.P32 (IO39), U4.P32 (IO39), U5.P32 (IO39)
unnamed: U1.IO40, U1.P33 (IO40), U1.Q33 (IO40), U2.IO40, U2.P33 (IO40), U2.Q33 (IO40), U3.P33 (IO40), U4.P33 (IO40), U5.P33 (IO40)
unnamed: U1.IO41, U1.P34 (IO41), U1.Q34 (IO41), U2.IO41, U2.P34 (IO41), U2.Q34 (IO41), U3.P34 (IO41), U4.P34 (IO41), U5.P34 (IO41)
unnamed: U1.IO42, U1.P35 (IO42), U1.Q35 (IO42), U2.IO42, U2.P35 (IO42), U2.Q35 (IO42), U3.P35 (IO42), U4.P35 (IO42), U5.P35 (IO42)
unnamed: U1.P36 (RXD), U1.Q36 (RXD), U1.RXD, U2.P36 (RXD), U2.Q36 (RXD), U2.RXD, U3.P36 (RXD), U4.P36 (RXD), U5.P36 (RXD)
unnamed: U1.P37 (TXD), U1.Q37 (TXD), U1.TXD, U2.P37 (TXD), U2.Q37 (TXD), U2.TXD, U3.P37 (TXD), U4.P37 (TXD), U5.P37 (TXD)
unnamed: U1.IO2, U1.P38 (IO2), U1.Q38 (IO2), U2.IO2, U2.P38 (IO2), U2.Q38 (IO2), U3.P38 (IO2), U4.P38 (IO2), U5.P38 (IO2)
unnamed: U1.IO1, U1.P39 (IO1), U1.Q39 (IO1), U2.IO1, U2.P39 (IO1), U2.Q39 (IO1), U3.P39 (IO1), U4.P39 (IO1), U5.P39 (IO1)
unnamed: U1.GND, U1.P40 (GND), U1.Q40 (GND), U2.GND, U2.P40 (GND), U2.Q40 (GND), U3.P40 (GND), U4.P40 (GND), U5.P40 (GND)
unnamed: X1.P1, X2.P1, X3.P1
unnamed: X1.P2, X2.P2, X3.P2
unnamed: X1.P3, X2.P3, X3.P3
unnamed: X1.P4, X2.P4, X3.P4
unnamed: X1.P5, X2.P5, X3.P5
unnamed: X1.P6, X2.P6, X3.P6
unnamed: X1.P7, X2.P7, X3.P7
unnamed: X1.P8, X2.P8, X3.P8
unnamed: X1.P9, X2.P9, X3.P9
unnamed: X1.P10, X2.P10, X3.P10
unnamed: X1.P11, X2.P11, X3.P11
unnamed: X1.P12, X2.P12, X3.P12
unnamed: X1.P13, X2.P13, X3.P13
unnamed: X4.P1, X5.P1, X6.P1
unnamed: X4.P2, X5.P2, X6.P2
unnamed: X4.P3, X5.P3, X6.P3
unnamed: X4.P4, X5.P4, X6.P4
unnamed: X4.P5, X5.P5, X6.P5
unnamed: X4.P6, X5.P6, X6.P6
unnamed: X4.P7, X5.P7, X6.P7
unnamed: X4.P8, X5.P8, X6.P8
unnamed: X4.P9, X5.P9, X6.P9
unnamed: X4.P10, X5.P10, X6.P10
unnamed: X4.P11, X5.P11, X6.P11
unnamed: X4.P12, X5.P12, X6.P12
unnamed: X4.P13, X5.P13, X6.P13
V_USB: J1.P1 (1), J1.P2 (2), J1.P3 (3), J1.P4 (4), U1.VUSB, U2.VUSB

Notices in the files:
parts and their libraries:
SparkFun-Aesthetics: Licensing: Creative Commons ShareAlike 4.0 International - https://creativecommons.org/licenses/by-sa/4.0
